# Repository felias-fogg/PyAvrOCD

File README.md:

#  PyAvrOCD

<p align="center">
  
</p>

PyAvrOCD is a GDB server for 8-bit AVR MCUs (see [list of supported MCUs](https://felias-fogg.github.io/PyAvrOCD/supported-mcus/) and [supported boards](https://felias-fogg.github.io/PyAvrOCD/supported-boards/)),  communicating with debug probes such as [Snap](https://www.microchip.com/en-us/development-tool/pg164100) or [Dragon](https://www.microchip.com/en-us/development-tool/atavrdragon). So, is it simply [another open-source GDB server for AVR MCUs](https://arduino-craft-corner.de/index.php/2026/02/10/pyavrocd-1-0-0-released/#what-are-alternatives-to-pyavrocd)? No! It is a *cross-platform* AVR GDB server. This means that it was easily possible to integrate it into [Arduino IDE 2](https://www.arduino.cc/en/software/) and [PlatformIO](https://platformio.org) board packages, bringing AVR debugging to these IDEs. Additionally, PyAvrOCD excels in [minimizing flash wear](https://arduino-craft-corner.de/index.php/2025/05/05/stop-and-go/) and [protects single-stepping against interrupts](https://arduino-craft-corner.de/index.php/2025/03/19/interrupted-and-very-long-single-steps/).

Interested in giving PyAvrOCD a try? You are welcome to [install](https://pyavrocd.io/install/) it. Want to learn more about it? [Read the docs](https://pyavrocd.io). Any feedback, be it bug reports, crazy ideas, or praise, is welcome.

## What has been done so far, and what to expect in the future

Meanwhile, PyAvrOCD covers all debugWIRE, JTAG (Megas), and UPDI MCUs. I am unsure whether it makes sense to extend its coverage to Xmegas.

I made some leeway to integrate PyAvrOCD more tightly with *PlatformIO* and with the *Arduino Maker Workshop* VSCode extension.

Currently, I work on integrating more debug probes, such as the Dragon, and also DIY probes, such as serialUPDI.

 Finally, I am committed to fixing some of the more obvious bugs in the AVR part of the GDB debugger.

 There was the idea of basing everything on more recent versions of the GCC toolchain because it will probably solve a number of problems on the debugging front. My attempt at using the GCC 15.1 toolchain was abruptly stopped when I discovered that the compiler produces buggy debug information concerning local variables, whereas the old compiler works without a flaw at that point. I guess more research and/or debugging is necessary before GCC 15.1 is a viable solution.

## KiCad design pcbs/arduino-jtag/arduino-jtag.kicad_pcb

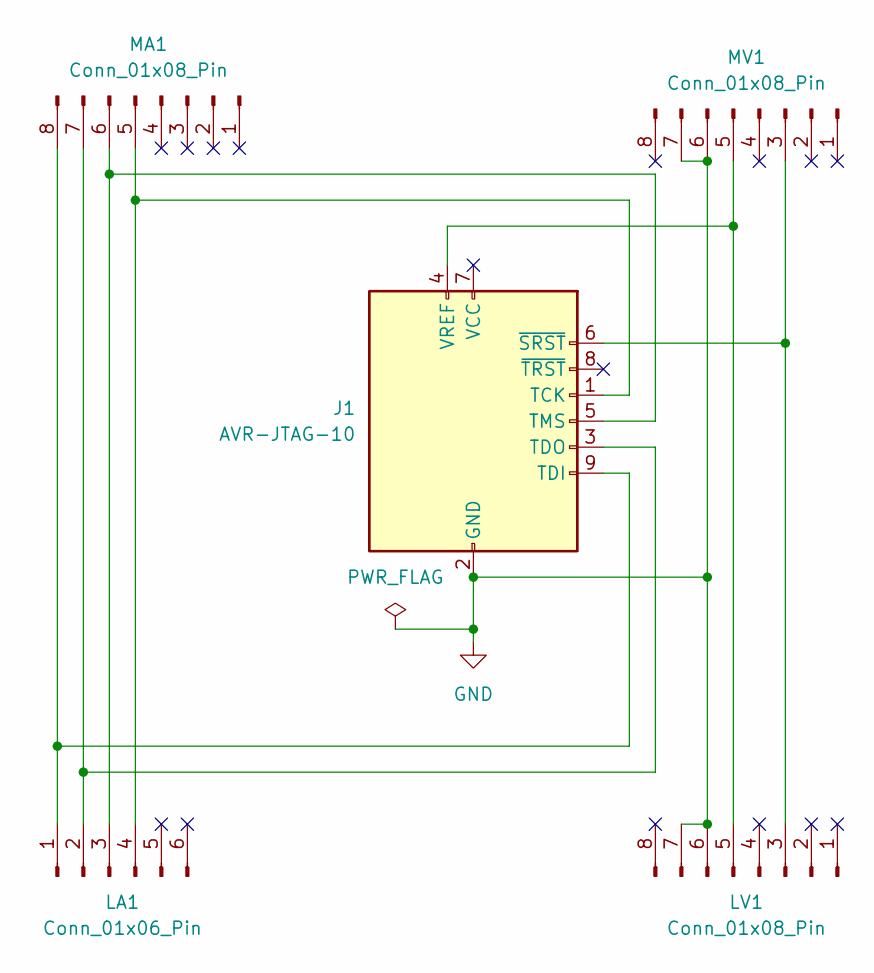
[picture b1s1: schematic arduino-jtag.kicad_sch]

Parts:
J1: AVR-JTAG-10; IDC-Header_2x05_P2.54mm_Vertical
LA1: Conn_01x06_Pin; PinHeader_1x06_P2.54mm_Vertical
LV1: Conn_01x08_Pin; PinHeader_1x08_P2.54mm_Vertical
MA1: Conn_01x08_Pin; PinHeader_1x08_P2.54mm_Vertical
MV1: Conn_01x08_Pin; PinHeader_1x08_P2.54mm_Vertical

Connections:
GND: J1.2 (GND), J1.10 (GND), LV1.6, LV1.7, MV1.6, MV1.7
unnamed: J1.1 (TCK), LA1.4, MA1.5
unnamed: J1.9 (TDI), LA1.1, MA1.8
unnamed: J1.3 (TDO), LA1.2, MA1.7
unnamed: J1.5 (TMS), LA1.3, MA1.6
unnamed: J1.4 (VREF), LV1.5, MV1.5
unnamed: J1.6 (~SRST), LV1.3, MV1.3

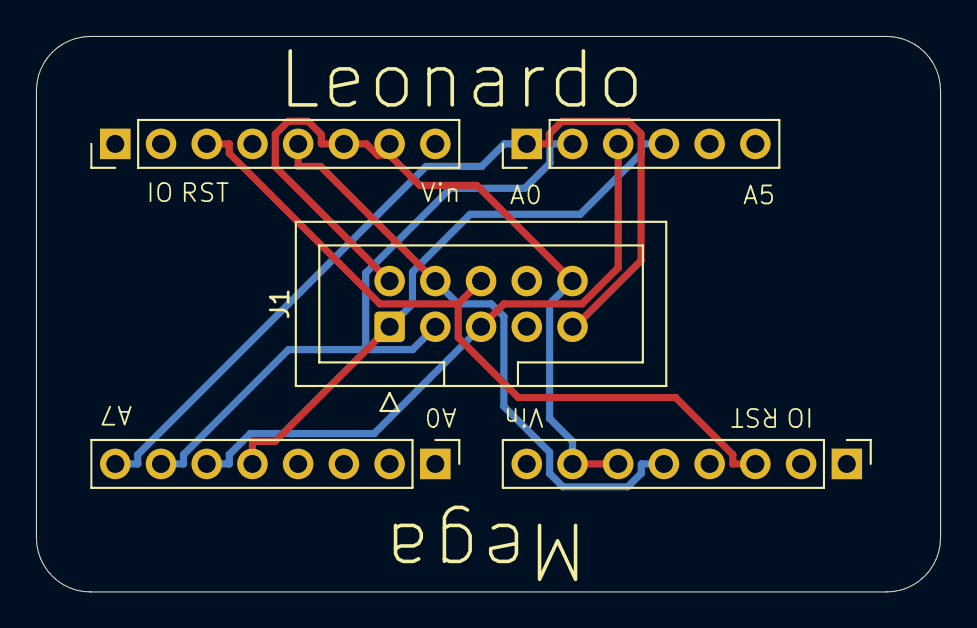
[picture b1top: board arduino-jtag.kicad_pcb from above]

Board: 2 copper layers, 50.2 x 30.9 mm, 5 parts (0 on the bottom side), 7 nets.

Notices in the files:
README.md:
License: MIT
